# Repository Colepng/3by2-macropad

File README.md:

# 3by2-macropad
I don't suggest actually making this.
I based this off of a handwired macropad that I actually use to test my keyboardrs lib

# Other libs used
https://www.allaboutcircuits.com/electronic-components/datasheet/1N914--onsemi/
https://github.com/ncarandini/KiCad-RP-Pico

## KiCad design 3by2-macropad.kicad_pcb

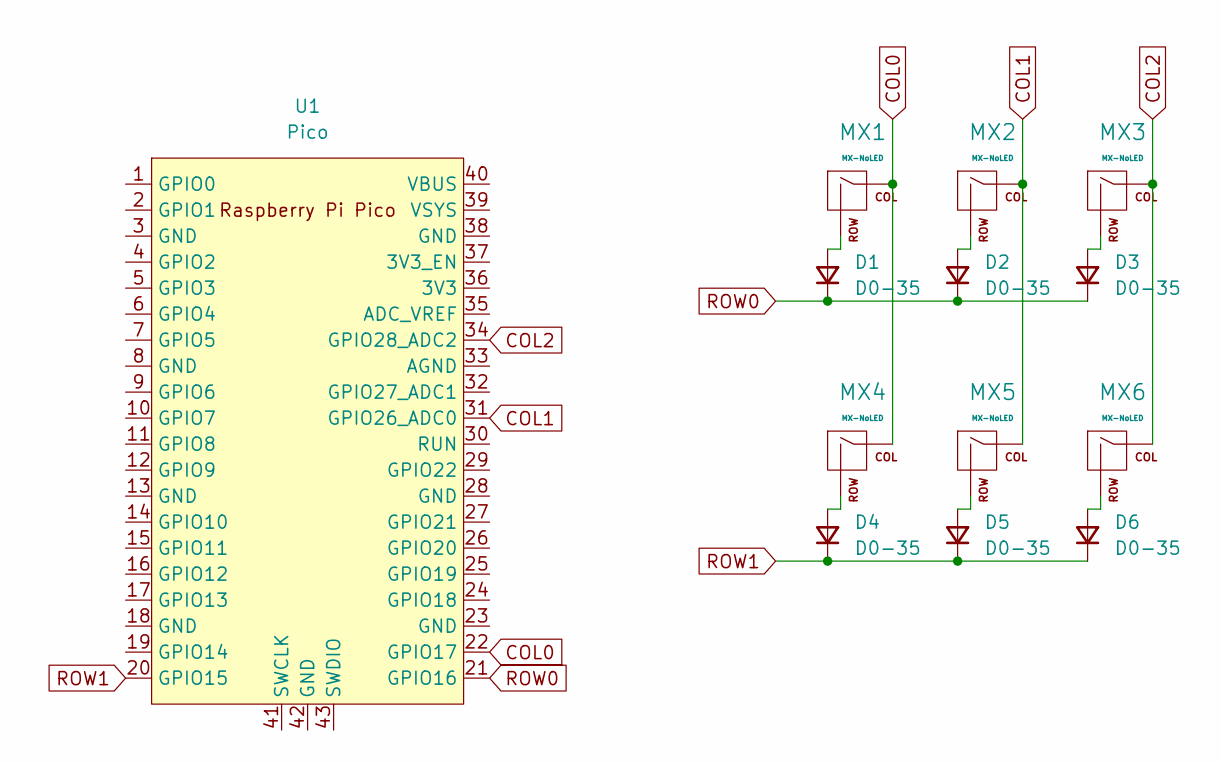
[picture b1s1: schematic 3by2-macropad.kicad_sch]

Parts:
D1, D2, D3, D4, D5, D6: D0-35; ON_Semiconductor-017AG-08_2016-O-MFG
MX1, MX2, MX3, MX4, MX5, MX6: MX-NoLED; MX-1U-NoLED
U1: Pico; RPi_Pico_SMD_TH

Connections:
COL0: MX1.1 (COL), MX4.1 (COL), U1.22 (GPIO17)
COL1: MX2.1 (COL), MX5.1 (COL), U1.31 (GPIO26_ADC0)
COL2: MX3.1 (COL), MX6.1 (COL), U1.34 (GPIO28_ADC2)
unnamed: D1.2 (A), MX1.2 (ROW)
unnamed: D2.2 (A), MX2.2 (ROW)
unnamed: D3.2 (A), MX3.2 (ROW)
unnamed: D4.2 (A), MX4.2 (ROW)
unnamed: D5.2 (A), MX5.2 (ROW)
unnamed: D6.2 (A), MX6.2 (ROW)
ROW0: D1.1 (K), D2.1 (K), D3.1 (K), U1.21 (GPIO16)
ROW1: D4.1 (K), D5.1 (K), D6.1 (K), U1.20 (GPIO15)

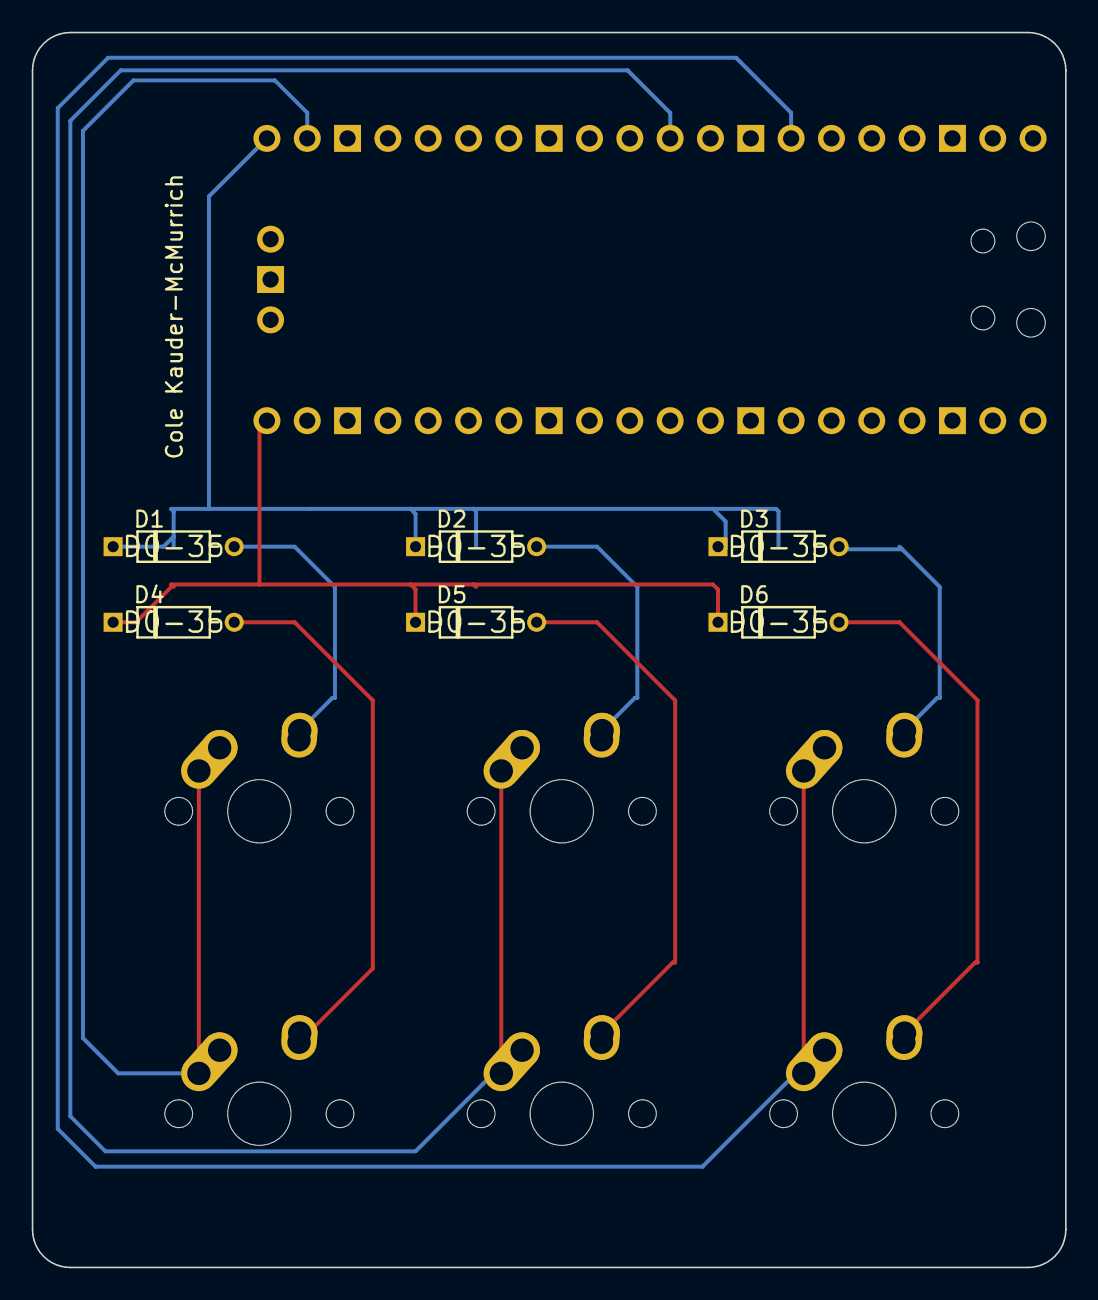
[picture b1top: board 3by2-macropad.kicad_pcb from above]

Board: 2 copper layers, 65.1 x 77.8 mm, 13 parts (1 on the bottom side), 11 nets.

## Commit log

2023-05-18 init project
2023-05-18 Add libs
2023-05-18 Add libs to kicad
2023-05-19 Done
2023-05-19 Used correct diode
